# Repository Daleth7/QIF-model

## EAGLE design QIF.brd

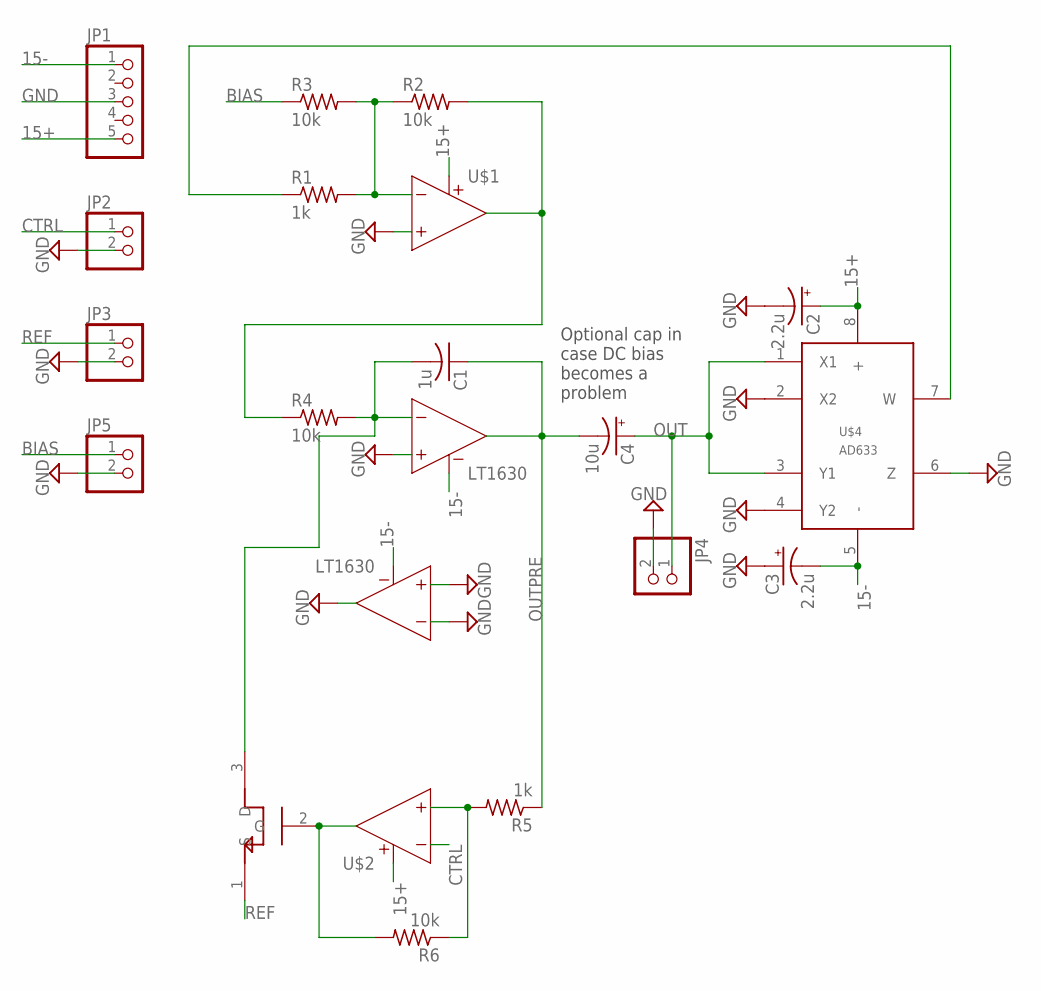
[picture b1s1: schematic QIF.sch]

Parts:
C1: 1u; C050-030X075
C2, C3: 2.2u; E2,5-6E
C4: 10u; E2,5-6
JP1: PINHD-1X5; 1X05
JP2, JP3, JP4, JP5: PINHD-1X2; 1X02
R1, R5: 1k; 0207/10
R2, R6: 10k; 0309V
R3, R4: 10k; 0207/10
U$1, U$2: LT1630; DIL8
U$3: 2N7000; TO-92
U$4: AD633; DIL8

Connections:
15+: C2.+, JP1.5, U$1.8 (V+), U$2.8 (V+), U$4.8 (+)
15-: C3.-, JP1.1, U$1.4 (V-), U$2.4 (V-), U$4.5 (-)
BIAS: JP5.1, R3.1
CTRL: JP2.1, U$2.2 (IN-)
GND: C2.-, C3.+, JP1.3, JP2.2, JP3.2, JP4.2, JP5.2, U$1.3 (IN+), U$1.5 (IN+1), U$2.5 (IN+1), U$2.6 (IN-1), U$2.7 (OUT1), U$4.2 (X2), U$4.4 (Y2), U$4.6 (Z)
unnamed: C1.2, R4.2, U$1.6 (IN-1), U$3.3 (D)
unnamed: R1.2, R2.1, R3.2, U$1.2 (IN-)
unnamed: R5.2, R6.1, U$2.3 (IN+)
unnamed: R2.2, R4.1, U$1.1 (OUT)
unnamed: R6.2, U$2.1 (OUT), U$3.2 (G)
unnamed: R1.1, U$4.7 (W)
OUT: C4.+, JP4.1, U$4.1 (X1), U$4.3 (Y1)
OUTPRE: C1.1, C4.-, R5.1, U$1.7 (OUT1)
REF: JP3.1, U$3.1 (S)

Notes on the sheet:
Optional cap in case DC bias becomes a problem

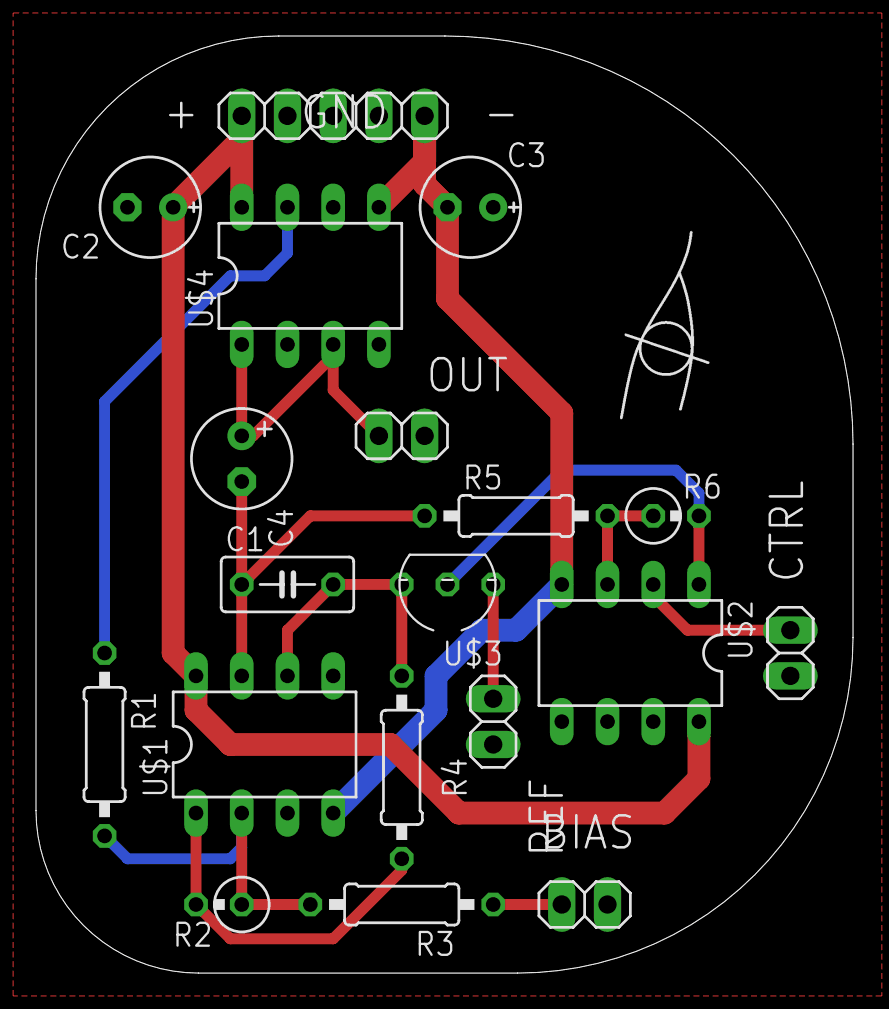
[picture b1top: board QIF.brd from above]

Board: 2 copper layers, 45.4 x 52.1 mm, 20 parts (0 on the bottom side), 14 nets.

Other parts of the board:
U$5: LOGO

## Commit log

2015-12-26 Initial commit -- Report and schematic only
2016-01-04 Added images and eagleCAD files
2016-01-04 Removed Word version
